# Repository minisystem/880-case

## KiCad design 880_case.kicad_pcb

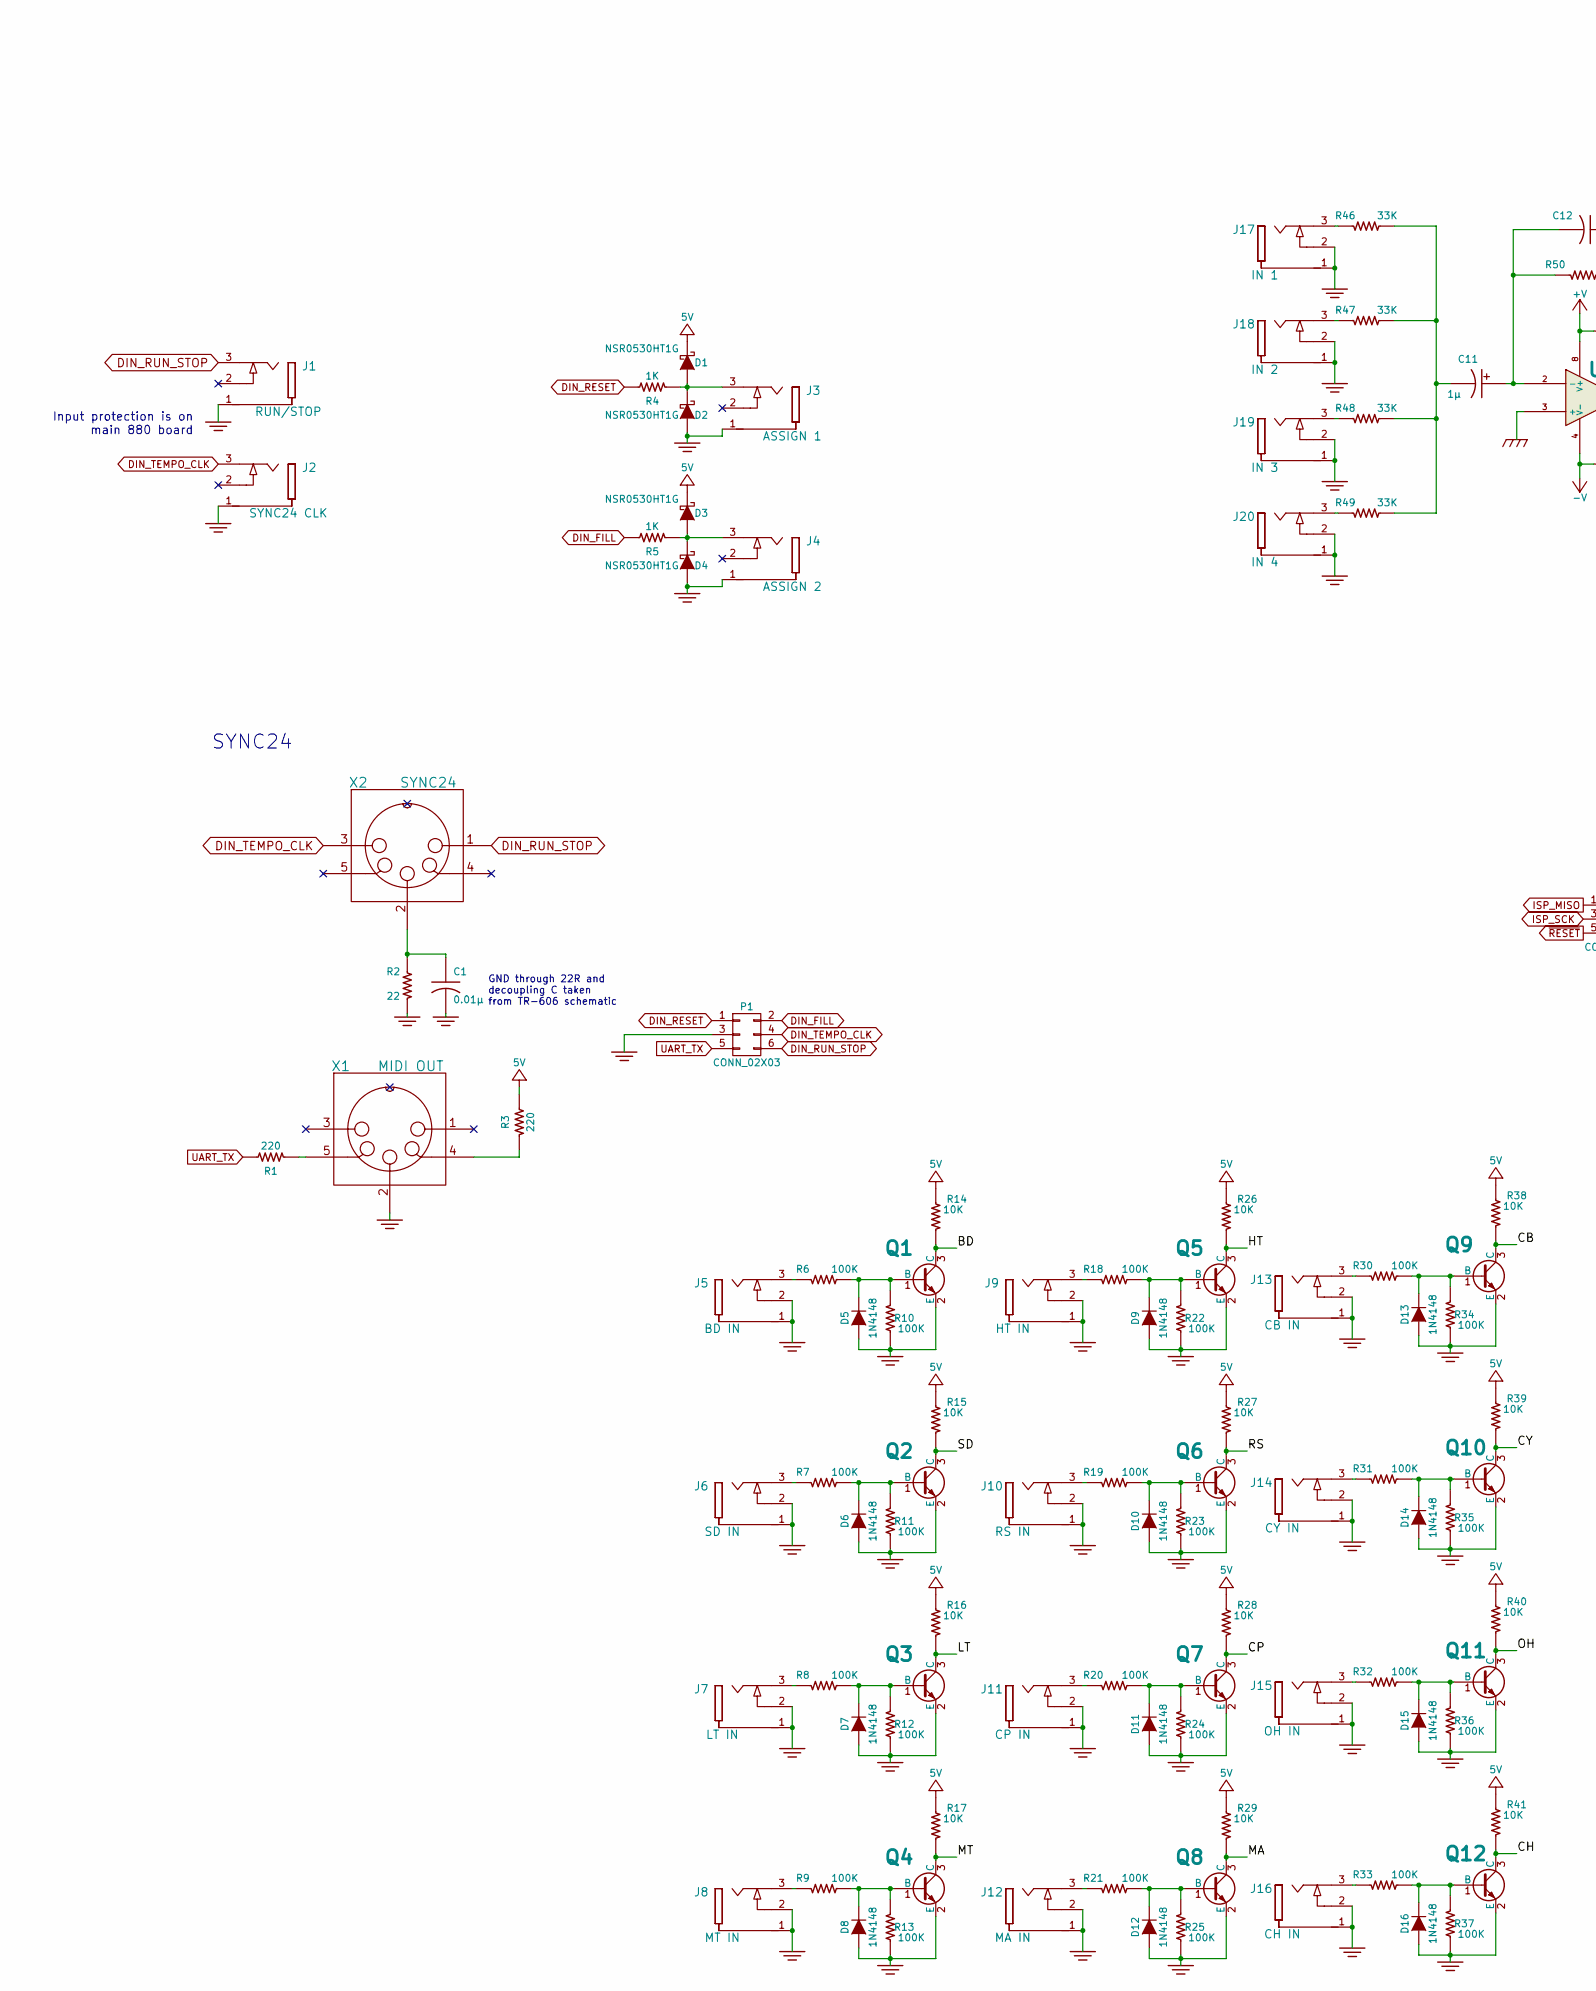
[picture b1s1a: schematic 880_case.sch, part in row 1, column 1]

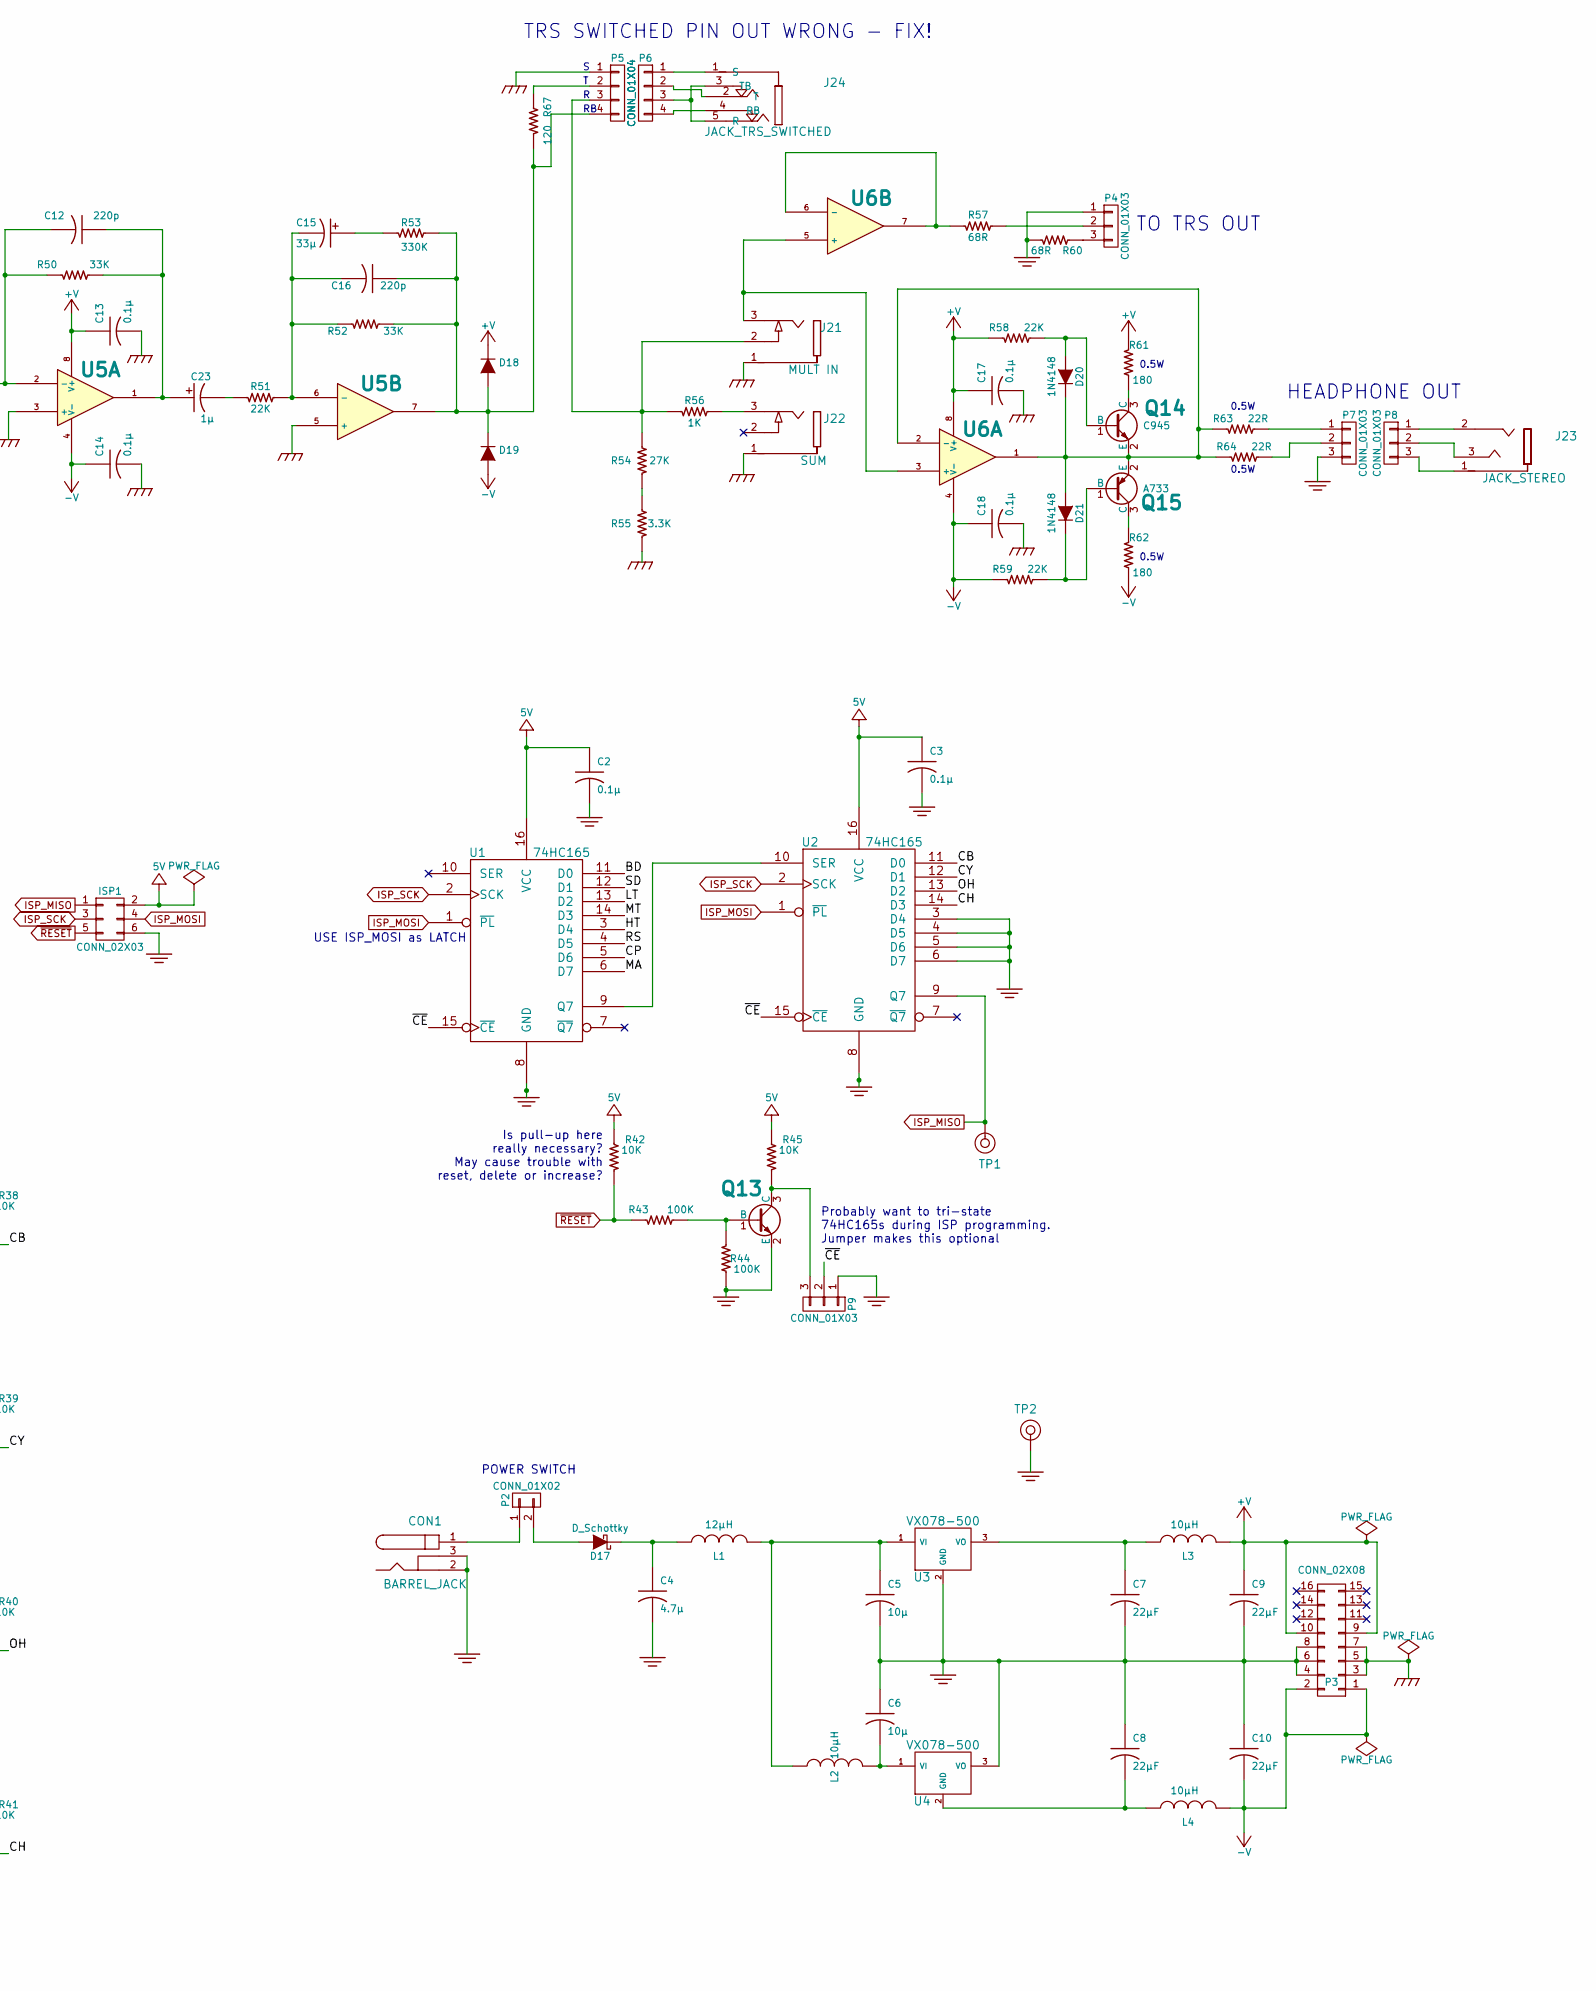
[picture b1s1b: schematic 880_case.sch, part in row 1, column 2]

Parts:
C1: 0.01µ; SM0603-C-MURATA
C2, C3, C13, C14, C17, C18: 0.1µ; SM0603-C-MURATA
C4: 4.7µ; C_1206
C5, C6: 10µ; C_1206
C7, C8, C9, C10: 22µF; C_1206
C11, C23: 1μ; CP_Elec_4x5.3
C12, C16: 220p; SM0603-C-MURATA
C15: 33μ; CP_Elec_5x5.3
CON1: BARREL_JACK; 712A-DC-JACK
D1, D2, D3, D4: NSR0530HT1G; SOD323-C1A2
D5, D6, D7, D8, D9, D10, D11, D12, D13, D14, D15, D16, D18, D19, D20, D21: 1N4148; SOD323-C1A2
D17: D_Schottky; SMB-1C2A
ISP1: CONN_02X03; vasch_strip_3x2
J1: RUN/STOP; PJ-301B-JACK-SLOTS
J2: SYNC24 CLK; PJ-301B-JACK-SLOTS
J3: ASSIGN 1; PJ-301B-JACK-SLOTS
J4: ASSIGN 2; PJ-301B-JACK-SLOTS
J5: BD IN; PJ-301B-JACK-SLOTS
J6: SD IN; PJ-301B-JACK-SLOTS
J7: LT IN; PJ-301B-JACK-SLOTS
J8: MT IN; PJ-301B-JACK-SLOTS
J9: HT IN; PJ-301B-JACK-SLOTS
J10: RS IN; PJ-301B-JACK-SLOTS
J11: CP IN; PJ-301B-JACK-SLOTS
J12: MA IN; PJ-301B-JACK-SLOTS
J13: CB IN; PJ-301B-JACK-SLOTS
J14: CY IN; PJ-301B-JACK-SLOTS
J15: OH IN; PJ-301B-JACK-SLOTS
J16: CH IN; PJ-301B-JACK-SLOTS
J17: IN 1; PJ-301B-JACK-SLOTS
J18: IN 2; PJ-301B-JACK-SLOTS
J19: IN 3; PJ-301B-JACK-SLOTS
J20: IN 4; PJ-301B-JACK-SLOTS
J21: MULT IN; PJ-301B-JACK-SLOTS
J22: SUM; PJ-301B-JACK-SLOTS
J23: JACK_STEREO; SJ1-3523N
J24: JACK_TRS_SWITCHED; RA49B14B_SWITCHCRAFT
L1: 12µH; SM0805-HAND
L2, L3, L4: 10µH; SM0805-HAND
P1: CONN_02X03; vasch_strip_3x2
P2: CONN_01X02; Pin_Header_Straight_1x02_Pitch2.54mm
P3: CONN_02X08; vasch_strip_5x2
P4, P7, P8, P9: CONN_01X03; Pin_Header_Straight_1x03_Pitch2.54mm
P5, P6: CONN_01X04; Pin_Header_Straight_1x04_Pitch2.54mm
Q1, Q2, Q3, Q4, Q5, Q6, Q7, Q8, Q9, Q10, Q11, Q12, Q13: MMBT3904; SOT23-132-JRL
Q14: C945; SOT-23
Q15: A733; SOT-23
R1, R3: 220; SM0603-R-YAGEO
R2: 22; SM0603-R-YAGEO
R4, R5, R56: 1K; SM0603-R-YAGEO
R6, R7, R8, R9, R10, R11, R12, R13, R18, R19, R20, R21, R22, R23, R24, R25, R30, R31, R32, R33, R34, R35, R36, R37, R43, R44: 100K; SM0603-R-YAGEO
R14, R15, R16, R17, R26, R27, R28, R29, R38, R39, R40, R41, R42, R45: 10K; SM0603-R-YAGEO
R46, R47, R48, R49, R50, R52: 33K; SM0603-R-YAGEO
R51, R58, R59: 22K; SM0603-R-YAGEO
R53: 330K; SM0603-R-YAGEO
R54: 27K; SM0603-R-YAGEO
R55: 3.3K; SM0603-R-YAGEO
R57, R60: 68R; SM0603-R-YAGEO
R61, R62: 180; R_0805
R63, R64: 22R; R_0805
R67: 120; R_0805
TP1, TP2: CONN_1; TEST_POINT_LOOP_4592
U1, U2: 74HC165; TSSOP-16_4.4x5mm_Pitch0.65mm
U3, U4: VX078-500; R-78E-0.5
U5, U6: 4558; TSSOP-8_3x3mm_Pitch0.65mm
X1: MIDI OUT; SD-50BV-5DIN
X2: SYNC24; SD-50BV-5DIN

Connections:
+5V: C2.1, C3.1, D1.1 (K), D3.1 (K), ISP1.2, R3.2, R14.1, R15.1, R16.1, R17.1, R26.1, R27.1, R28.1, R29.1, R38.1, R39.1, R40.1, R41.1, R42.1, R45.1, U1.16 (VCC), U2.16 (VCC)
+V: C9.1, C13.1, C17.1, D18.1 (K), L3.2, P3.9, P3.10, R58.1, R61.1, U5.8 (V+), U6.8 (V+)
-V: C10.2, C14.1, C18.1, D19.2 (A), L4.2, P3.1, P3.2, R59.1, R62.2, U5.4 (V-), U6.4 (V-)
/BD: Q1.3 (C), R14.2, U1.11 (D0)
/CB: Q9.3 (C), R38.2, U2.11 (D0)
/CH: Q12.3 (C), R41.2, U2.14 (D3)
/CP: Q7.3 (C), R28.2, U1.5 (D6)
/CY: Q10.3 (C), R39.2, U2.12 (D1)
/HT: Q5.3 (C), R26.2, U1.3 (D4)
/LT: Q3.3 (C), R16.2, U1.13 (D2)
/MA: Q8.3 (C), R29.2, U1.6 (D7)
/MT: Q4.3 (C), R17.2, U1.14 (D3)
/OH: Q11.3 (C), R40.2, U2.13 (D2)
/RS: Q6.3 (C), R27.2, U1.4 (D5)
/SD: Q2.3 (C), R15.2, U1.12 (D1)
/~CE: P9.2, U1.15 (~CE), U2.15 (~CE)
DIN_FILL: P1.2, R5.2
DIN_RESET: P1.1, R4.2
DIN_RUN_STOP: J1.3, P1.6, X2.1
DIN_TEMPO_CLK: J2.3, P1.4, X2.3
ISP_MISO: ISP1.1, TP1.1, U2.9 (Q7)
ISP_MOSI: ISP1.4, U1.1 (~PL), U2.1 (~PL)
ISP_SCK: ISP1.3, U1.2 (SCK), U2.2 (SCK)
unnamed: C1.1, R2.2, X2.2
unnamed: C4.1, D17.1 (K), L1.1
unnamed: C5.1, L1.2, L2.1, U3.1 (VI)
unnamed: C6.2, L2.2, U4.1 (VI)
unnamed: C7.1, L3.1, U3.3 (VO)
unnamed: C8.2, L4.1, U4.2 (GND)
unnamed: C11.1 (+), C12.2, R50.1, U5.2 (-)
unnamed: C11.2 (-), R46.2, R47.2, R48.2, R49.2
unnamed: C12.1, C23.1 (+), R50.2, U5.1
unnamed: C15.1 (+), R53.1
unnamed: C15.2 (-), C16.2, R51.2, R52.1, U5.6 (-)
unnamed: C16.1, D18.2 (A), D19.1 (K), P5.4, R52.2, R53.2, R67.1, U5.7
unnamed: C23.2 (-), R51.1
unnamed: CON1.1, P2.1
unnamed: D1.2 (A), D2.1 (K), J3.3, R4.1
unnamed: D3.2 (A), D4.1 (K), J4.3, R5.1
unnamed: D5.1 (K), Q1.1 (B), R6.2, R10.1
unnamed: D6.1 (K), Q2.1 (B), R7.2, R11.1
unnamed: D7.1 (K), Q3.1 (B), R8.2, R12.1
unnamed: D8.1 (K), Q4.1 (B), R9.2, R13.1
unnamed: D9.1 (K), Q5.1 (B), R18.2, R22.1
unnamed: D10.1 (K), Q6.1 (B), R19.2, R23.1
unnamed: D11.1 (K), Q7.1 (B), R20.2, R24.1
unnamed: D12.1 (K), Q8.1 (B), R21.2, R25.1
unnamed: D13.1 (K), Q9.1 (B), R30.2, R34.1
unnamed: D14.1 (K), Q10.1 (B), R31.2, R35.1
unnamed: D15.1 (K), Q11.1 (B), R32.2, R36.1
unnamed: D16.1 (K), Q12.1 (B), R33.2, R37.1
unnamed: D17.2 (A), P2.2
unnamed: D20.1 (K), D21.2 (A), Q14.2 (E), Q15.2 (E), R63.1, R64.1, U6.1, U6.2 (-)
unnamed: D20.2 (A), Q14.1 (B), R58.2
unnamed: D21.1 (K), Q15.1 (B), R59.2
unnamed: J5.3, R6.1
unnamed: J6.3, R7.1
unnamed: J7.3, R8.1
unnamed: J8.3, R9.1
unnamed: J9.3, R18.1
unnamed: J10.3, R19.1
unnamed: J11.3, R20.1
unnamed: J12.3, R21.1
unnamed: J13.3, R30.1
unnamed: J14.3, R31.1
unnamed: J15.3, R32.1
unnamed: J16.3, R33.1
unnamed: J17.3, R46.1
unnamed: J18.3, R47.1
unnamed: J19.3, R48.1
unnamed: J20.3, R49.1
unnamed: J21.2, P5.3, R54.2, R56.2
unnamed: J21.3, U6.3 (+), U6.5 (+)
unnamed: J22.3, R56.1
unnamed: J23.1, P8.3
unnamed: J23.2, P8.1
unnamed: J23.3, P8.2
unnamed: J24.1 (S), P6.1
unnamed: J24.2 (T), P6.2
unnamed: J24.3 (TB), J24.5 (R), P6.3
unnamed: J24.4 (RB), P6.4
unnamed: P4.2, R57.1
unnamed: P4.3, R60.1
unnamed: P5.2, R67.2
unnamed: P7.1, R63.2
unnamed: P7.2, R64.2
unnamed: P9.3, Q13.3 (C), R45.2
unnamed: Q13.1 (B), R43.2, R44.1
unnamed: Q14.3 (C), R61.2
unnamed: Q15.3 (C), R62.1
unnamed: R1.1, X1.5
unnamed: R3.1, X1.4
unnamed: R54.1, R55.2
unnamed: R57.2, U6.6 (-), U6.7
unnamed: U1.9 (Q7), U2.10 (SER)
UART_TX: P1.5, R1.2
~RESET: ISP1.5, R42.2, R43.1

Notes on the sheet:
SYNC24
GND through 22R and decoupling C taken from TR-606 schematic
Probably want to tri-state 74HC165s during ISP programming. Jumper makes this optional
POWER SWITCH
TO TRS OUT
0.5W
HEADPHONE OUT
USE ISP_MOSI as LATCH
Is pull-up here really necessary? May cause trouble with reset, delete or increase?
Input protection is on main 880 board
TRS SWITCHED PIN OUT WRONG - FIX!

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
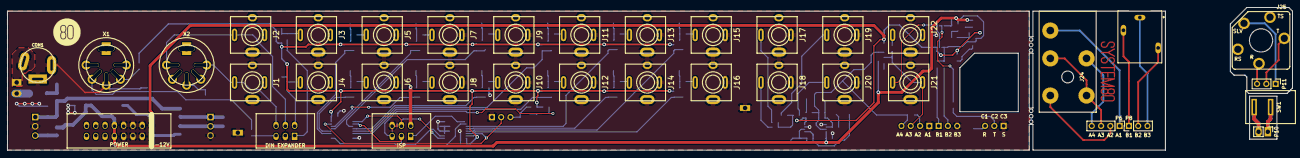
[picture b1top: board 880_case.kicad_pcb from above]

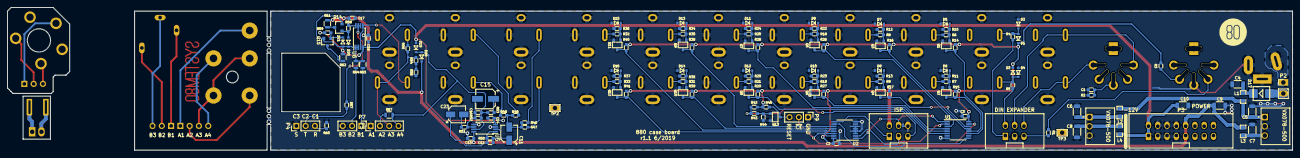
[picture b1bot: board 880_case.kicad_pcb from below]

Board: 2 copper layers, 316.8 x 38.0 mm, 179 parts (140 on the bottom side), 103 nets.

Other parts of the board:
HOLE-M3, HOLE-M3#2, HOLE-M3#3, HOLE-M3#4, HOLE-M3#5, HOLE-M3#6: VAL**; HOLE-M3
J25: JACK_STEREO; 11XPC-SWITCH_CRAFT
P10: CONN_01X02; Pin_Header_Straight_1x02_Pitch2.54mm
P11: CONN_01X03; Pin_Header_Straight_1x03_Pitch2.54mm
SW1: SPST; PR_PPR_ROCKER_SW
TP3: CONN_1; TEST_POINT_LOOP_4592

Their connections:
unnamed: J25.1, P11.1
unnamed: J25.2, P11.2
unnamed: J25.3, P11.3
unnamed: P10.1, SW1.2
unnamed: P10.2, SW1.1

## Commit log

2019-01-24 added mixer plus balanced out
2019-01-27 added headphone output
2019-01-27 schematic complete, about to do erc and export netlist
2019-01-28 started layout
2019-01-29 more component placement
2019-01-30 more placement
2019-02-02 added 3d models for DC jack, VX0-78XX-500 DC-DC converters, and stereo headhpone jack
2019-02-03 first route complete
2019-02-11 added insert on submix sum. put insert jack and headphone jack on daughter board
2019-02-12 place silkscreen references
2019-02-12 more tweaking, almost ready to order
2019-02-14 first prototype PCB ordered
2019-05-31 working on second revision, about to move headhpone amp circuit to align board-to-board connectors
2019-05-31 headphone amp components moved
2019-06-01 more edits
2019-06-03 added power switch and balanced jack sub boards
2019-06-04 stuff
2019-06-09 panelizing pcb
2019-06-10 panelized sub-boards
2019-06-12 v1.1 ordered plus sub boards
2019-09-22 commit before checkout of new branch
2019-09-23 separating digital and audio gnd planes
2019-09-24 working on 4 layer, separate digital and audio gnd planes
2019-09-26 routed
2019-09-27 4 layer, added tri-state buffer on MISO line, ordered prototype PCB
2020-01-16 few tweaks before panelizing. kept 74HCT1G125GV footprint as TSOP-5-SC74A-SOT-753, which is the larger of the two available footprints for U7
2020-02-04 getting ready to panelize for production
2020-09-25 first update in a long while. this version and gone through production
